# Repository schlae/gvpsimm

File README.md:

# GVP 64-pin SIMM modules

This repository contains reproduction SIMMs for GVP (Great Valley Products)
Amiga accelerator cards. Select a link below to pick a particular version.

[4MB version](4MB/README.md)

[16MB version](16MB/README.md)

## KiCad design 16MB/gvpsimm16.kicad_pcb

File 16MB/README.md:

# GVP-Compatible 64-Pin 16MB SIMM

*Warning: Beta Version! This has not been fabricated nor tested, build at your own risk*

This is a 16MB (4Mx32) SIMM design for certain GVP accelerator cards. It's
64-pin but follows the proprietary GVP pinout.

Since this is a beta version, fab files have not been generated. If you have
the expertise to get the files, load them in KiCad, and generate the fab
files, you're probably OK with doing some experimentation to get these working.

Board dimensions are 3.85 x 0.925 inches. It is a 4 layer board. When
ordering, **please specify a board thickness of 1.2mm!** This ensures that
it will fit in the SIMM slot. Again, to emphasize: most quick-turn board
services use 1.6mm thick boards by default which will not fit in a SIMM
slot. Be sure to select 1.2mm!

## DRAM Chips

KM44C4000AS-6, K4F1704110-FC60, HYB5116400BJ-60, or equivalent 60ns fast
page mode memory chips (16 megabit).

Be sure that the memory chip you select has a 12-bit row address and a 10-bit
column address -- sometimes known as "4K refresh" because a full refresh
must access all 4096 row addresses. It must also operate at 5V.

## Bypass Capacitors

Use eight 0603 capacitors with a value of at least 0.22uF. Ensure the voltage
rating is 10V or higher. Do not use 6.3V rated capacitors since they are too
close to the rail voltage of 5V.

## Assembly Notes

Since the chips are fairly close together, I recommend ordering the boards
with a solder stencil and using solder paste with a reflow process (or
hot plate) to solder the components.

## License

This project is licensed under the CERN Open Hardware License Version 2 - Permissive.

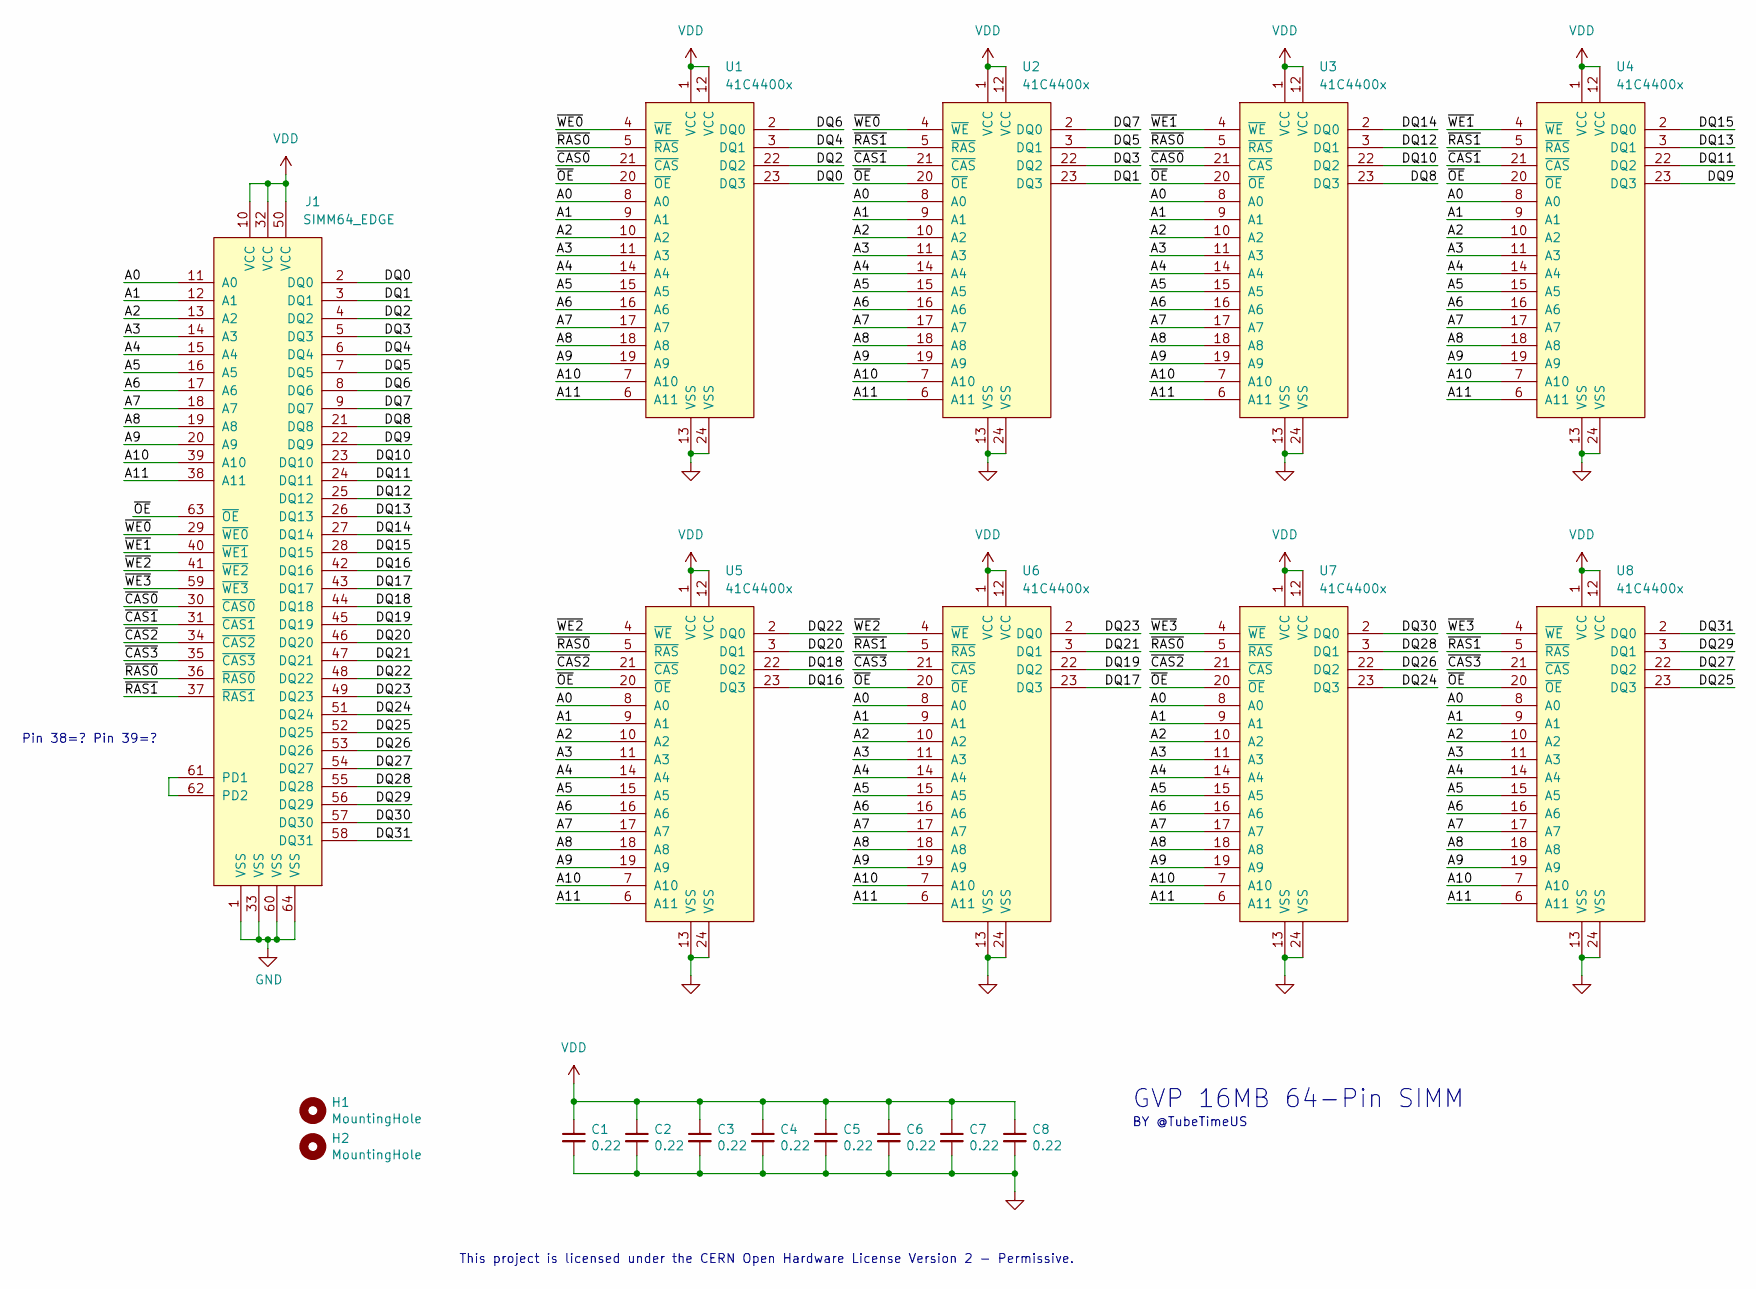
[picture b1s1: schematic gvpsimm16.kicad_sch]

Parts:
C1, C2, C3, C4, C5, C6, C7, C8: 0.22; CAPC1608X100
H1, H2: MountingHole; MH_125
J1: SIMM64_EDGE; EDGE_SIMM_64_127
U1, U2, U3, U4, U5, U6, U7, U8: 41C4400x; SOJ127P851X356-24

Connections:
/A0: J1.11 (A0), U1.8 (A0), U2.8 (A0), U3.8 (A0), U4.8 (A0), U5.8 (A0), U6.8 (A0), U7.8 (A0), U8.8 (A0)
/A1: J1.12 (A1), U1.9 (A1), U2.9 (A1), U3.9 (A1), U4.9 (A1), U5.9 (A1), U6.9 (A1), U7.9 (A1), U8.9 (A1)
/A2: J1.13 (A2), U1.10 (A2), U2.10 (A2), U3.10 (A2), U4.10 (A2), U5.10 (A2), U6.10 (A2), U7.10 (A2), U8.10 (A2)
/A3: J1.14 (A3), U1.11 (A3), U2.11 (A3), U3.11 (A3), U4.11 (A3), U5.11 (A3), U6.11 (A3), U7.11 (A3), U8.11 (A3)
/A4: J1.15 (A4), U1.14 (A4), U2.14 (A4), U3.14 (A4), U4.14 (A4), U5.14 (A4), U6.14 (A4), U7.14 (A4), U8.14 (A4)
/A5: J1.16 (A5), U1.15 (A5), U2.15 (A5), U3.15 (A5), U4.15 (A5), U5.15 (A5), U6.15 (A5), U7.15 (A5), U8.15 (A5)
/A6: J1.17 (A6), U1.16 (A6), U2.16 (A6), U3.16 (A6), U4.16 (A6), U5.16 (A6), U6.16 (A6), U7.16 (A6), U8.16 (A6)
/A7: J1.18 (A7), U1.17 (A7), U2.17 (A7), U3.17 (A7), U4.17 (A7), U5.17 (A7), U6.17 (A7), U7.17 (A7), U8.17 (A7)
/A8: J1.19 (A8), U1.18 (A8), U2.18 (A8), U3.18 (A8), U4.18 (A8), U5.18 (A8), U6.18 (A8), U7.18 (A8), U8.18 (A8)
/A9: J1.20 (A9), U1.19 (A9), U2.19 (A9), U3.19 (A9), U4.19 (A9), U5.19 (A9), U6.19 (A9), U7.19 (A9), U8.19 (A9)
/A10: J1.39 (A10), U1.7 (A10), U2.7 (A10), U3.7 (A10), U4.7 (A10), U5.7 (A10), U6.7 (A10), U7.7 (A10), U8.7 (A10)
/A11: J1.38 (A11), U1.6 (A11), U2.6 (A11), U3.6 (A11), U4.6 (A11), U5.6 (A11), U6.6 (A11), U7.6 (A11), U8.6 (A11)
/DQ0: J1.2 (DQ0), U1.23 (DQ3)
/DQ1: J1.3 (DQ1), U2.23 (DQ3)
/DQ2: J1.4 (DQ2), U1.22 (DQ2)
/DQ3: J1.5 (DQ3), U2.22 (DQ2)
/DQ4: J1.6 (DQ4), U1.3 (DQ1)
/DQ5: J1.7 (DQ5), U2.3 (DQ1)
/DQ6: J1.8 (DQ6), U1.2 (DQ0)
/DQ7: J1.9 (DQ7), U2.2 (DQ0)
/DQ8: J1.21 (DQ8), U3.23 (DQ3)
/DQ9: J1.22 (DQ9), U4.23 (DQ3)
/DQ10: J1.23 (DQ10), U3.22 (DQ2)
/DQ11: J1.24 (DQ11), U4.22 (DQ2)
/DQ12: J1.25 (DQ12), U3.3 (DQ1)
/DQ13: J1.26 (DQ13), U4.3 (DQ1)
/DQ14: J1.27 (DQ14), U3.2 (DQ0)
/DQ15: J1.28 (DQ15), U4.2 (DQ0)
/DQ16: J1.42 (DQ16), U5.23 (DQ3)
/DQ17: J1.43 (DQ17), U6.23 (DQ3)
/DQ18: J1.44 (DQ18), U5.22 (DQ2)
/DQ19: J1.45 (DQ19), U6.22 (DQ2)
/DQ20: J1.46 (DQ20), U5.3 (DQ1)
/DQ21: J1.47 (DQ21), U6.3 (DQ1)
/DQ22: J1.48 (DQ22), U5.2 (DQ0)
/DQ23: J1.49 (DQ23), U6.2 (DQ0)
/DQ24: J1.51 (DQ24), U7.23 (DQ3)
/DQ25: J1.52 (DQ25), U8.23 (DQ3)
/DQ26: J1.53 (DQ26), U7.22 (DQ2)
/DQ27: J1.54 (DQ27), U8.22 (DQ2)
/DQ28: J1.55 (DQ28), U7.3 (DQ1)
/DQ29: J1.56 (DQ29), U8.3 (DQ1)
/DQ30: J1.57 (DQ30), U7.2 (DQ0)
/DQ31: J1.58 (DQ31), U8.2 (DQ0)
/~CAS0: J1.30 (~CAS0), U1.21 (~CAS), U3.21 (~CAS)
/~CAS1: J1.31 (~CAS1), U2.21 (~CAS), U4.21 (~CAS)
/~CAS2: J1.34 (~CAS2), U5.21 (~CAS), U7.21 (~CAS)
/~CAS3: J1.35 (~CAS3), U6.21 (~CAS), U8.21 (~CAS)
/~OE: J1.63 (~OE), U1.20 (~OE), U2.20 (~OE), U3.20 (~OE), U4.20 (~OE), U5.20 (~OE), U6.20 (~OE), U7.20 (~OE), U8.20 (~OE)
/~RAS0: J1.36 (~RAS0), U1.5 (~RAS), U3.5 (~RAS), U5.5 (~RAS), U7.5 (~RAS)
/~RAS1: J1.37 (~RAS1), U2.5 (~RAS), U4.5 (~RAS), U6.5 (~RAS), U8.5 (~RAS)
/~WE0: J1.29 (~WE0), U1.4 (~WE), U2.4 (~WE)
/~WE1: J1.40 (~WE1), U3.4 (~WE), U4.4 (~WE)
/~WE2: J1.41 (~WE2), U5.4 (~WE), U6.4 (~WE)
/~WE3: J1.59 (~WE3), U7.4 (~WE), U8.4 (~WE)
GND: C1.2, C2.2, C3.2, C4.2, C5.2, C6.2, C7.2, C8.2, J1.1 (VSS), J1.33 (VSS), J1.60 (VSS), J1.64 (VSS), U1.13 (VSS), U1.24 (VSS), U2.13 (VSS), U2.24 (VSS), U3.13 (VSS), U3.24 (VSS), U4.13 (VSS), U4.24 (VSS), U5.13 (VSS), U5.24 (VSS), U6.13 (VSS), U6.24 (VSS), U7.13 (VSS), U7.24 (VSS), U8.13 (VSS), U8.24 (VSS)
unnamed: J1.61 (PD1), J1.62 (PD2)
VDD: C1.1, C2.1, C3.1, C4.1, C5.1, C6.1, C7.1, C8.1, J1.10 (VCC), J1.32 (VCC), J1.50 (VCC), U1.1 (VCC), U1.12 (VCC), U2.1 (VCC), U2.12 (VCC), U3.1 (VCC), U3.12 (VCC), U4.1 (VCC), U4.12 (VCC), U5.1 (VCC), U5.12 (VCC), U6.1 (VCC), U6.12 (VCC), U7.1 (VCC), U7.12 (VCC), U8.1 (VCC), U8.12 (VCC)

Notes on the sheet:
Pin 38=? Pin 39=?
BY @TubeTimeUS
This project is licensed under the CERN Open Hardware License Version 2 - Permissive.
GVP 16MB 64-Pin SIMM

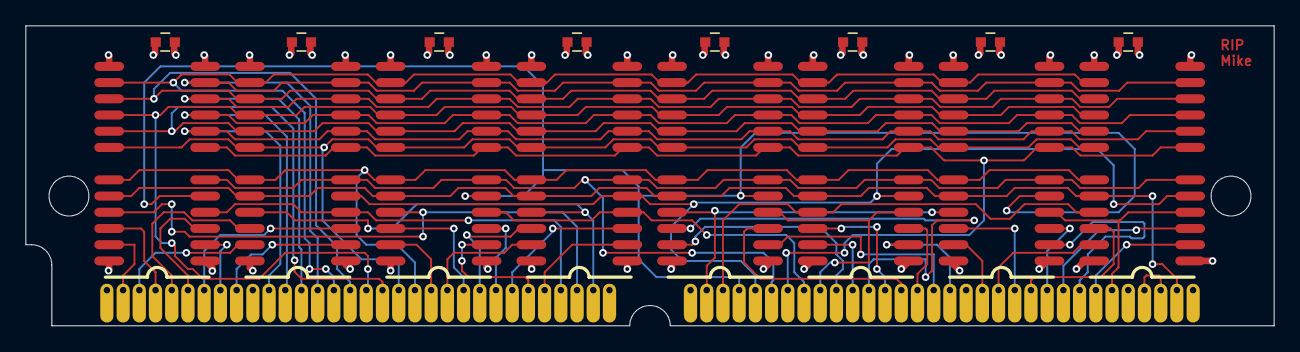
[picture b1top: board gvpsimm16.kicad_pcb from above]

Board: 4 copper layers, 97.8 x 23.5 mm, 19 parts (0 on the bottom side), 58 nets.

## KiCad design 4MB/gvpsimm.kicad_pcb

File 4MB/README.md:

# GVP-Compatible 64-Pin 4MB SIMM

GVP (Great Valley Products) made a number of Amiga accelerator cards back
in the 80s and 90s. Many of the accelerator cards accept 64-pin
memory modules; however they do not follow a standard pinout.

These GVP proprietary SIMMS are somewhat hard to find and expensive when
they do turn up. Others have reverse engineered the design, but these clones
use CAD tools that are not open source.

This design is based on a 4MB SIMM that came from my own GVP 68030
accelerator card. You can see my [epic build thread on Twitter](https://twitter.com/TubeTimeUS/status/1154195947125002240).

(The original SIMM is on the right, and on the left are my clones.)

Design files are here:

[Schematic](gvpsimm.pdf)

[Fab files](fab/gvpsimm_rev1.zip)

Board dimensions are 3.85 x 0.875 inches, and it is a 4 layer board. When
ordering the board, remember to specify a board thickness of 1.2mm. This
ensures it will fit in the SIMM slot.

## DRAM Chips

My original SIMM module uses the Hitachi HM514400CS-6 memory chips, which
are 1 Meg x 4 bit 60ns devices. Since there are eight memory chips, this
results in a memory array of 1 Meg x 32 bit, or 4 megabytes. I have built and
tested a large number of SIMMs with these chips and they all work fine.

There exist a number of memory chips which I have not tested (beware!) but are
likely compatible:
* Samsung KM44C1000DJ-6
* Mitsubishi M5M44400CJ-6
* NEC PD424400LA-60
* Toshiba TC514400ASJ-60
* TI TMS44400-60 DJ
* Micron MT4C4001JDJ-6

The list is from [this thread at Abime](http://eab.abime.net/showthread.php?t=86182).

## 1MB Variant

There exist 256K x 4 bit memories in the same package that are pin
compatible with the larger chip, and it can be installed instead,
yielding a 1MB SIMM. The difference is that pin 5 (A9 address line) is a
no-connect. I have not tested this configuration, but if you want to try it, I
found a couple of memory chips that might work.

* Samsung KM44C256DJ-6
* TI TMS44C256-60 DJ
* Mitsubishi M5M44256AJ-6

## Bypass Capacitors

Others have mistakenly assumed that the original GVP SIMM has no bypass
capacitors. This is not true--on detailed inspection I observed eight
ultra-low profile ceramic capacitors soldered directly underneath the
memory chips.

Ultra-low profile ceramic capacitors are hard to find now, and would
make assembly somewhat difficult. Instead of this I opted to use seven
standard 0603 ceramic capacitors placed in between the memory chips.
For best results, use 0.22uF or larger. Ensure the voltage rating is 10V
or higher, as 6.3V ceramics do not have sufficient derating for use at 5V.
Consider also that the capacitance of many ceramic capacitors decreases
significantly as the operating voltage nears the rated voltage, as much as
40%!

## Fabrication Notes

When you send the board out for fabrication, please specify a board
thickness of 1.2mm instead of the more common 1.6mm thickness. This
will ensure that the SIMM will fit correctly in the sockets.

Since the components are packed relatively close together, they can be
difficult to solder by hand. I recommend using a solder stencil and a
reflow process.

## License

This project is licensed under the CERN Open Hardware License Version 2 - Permissive.

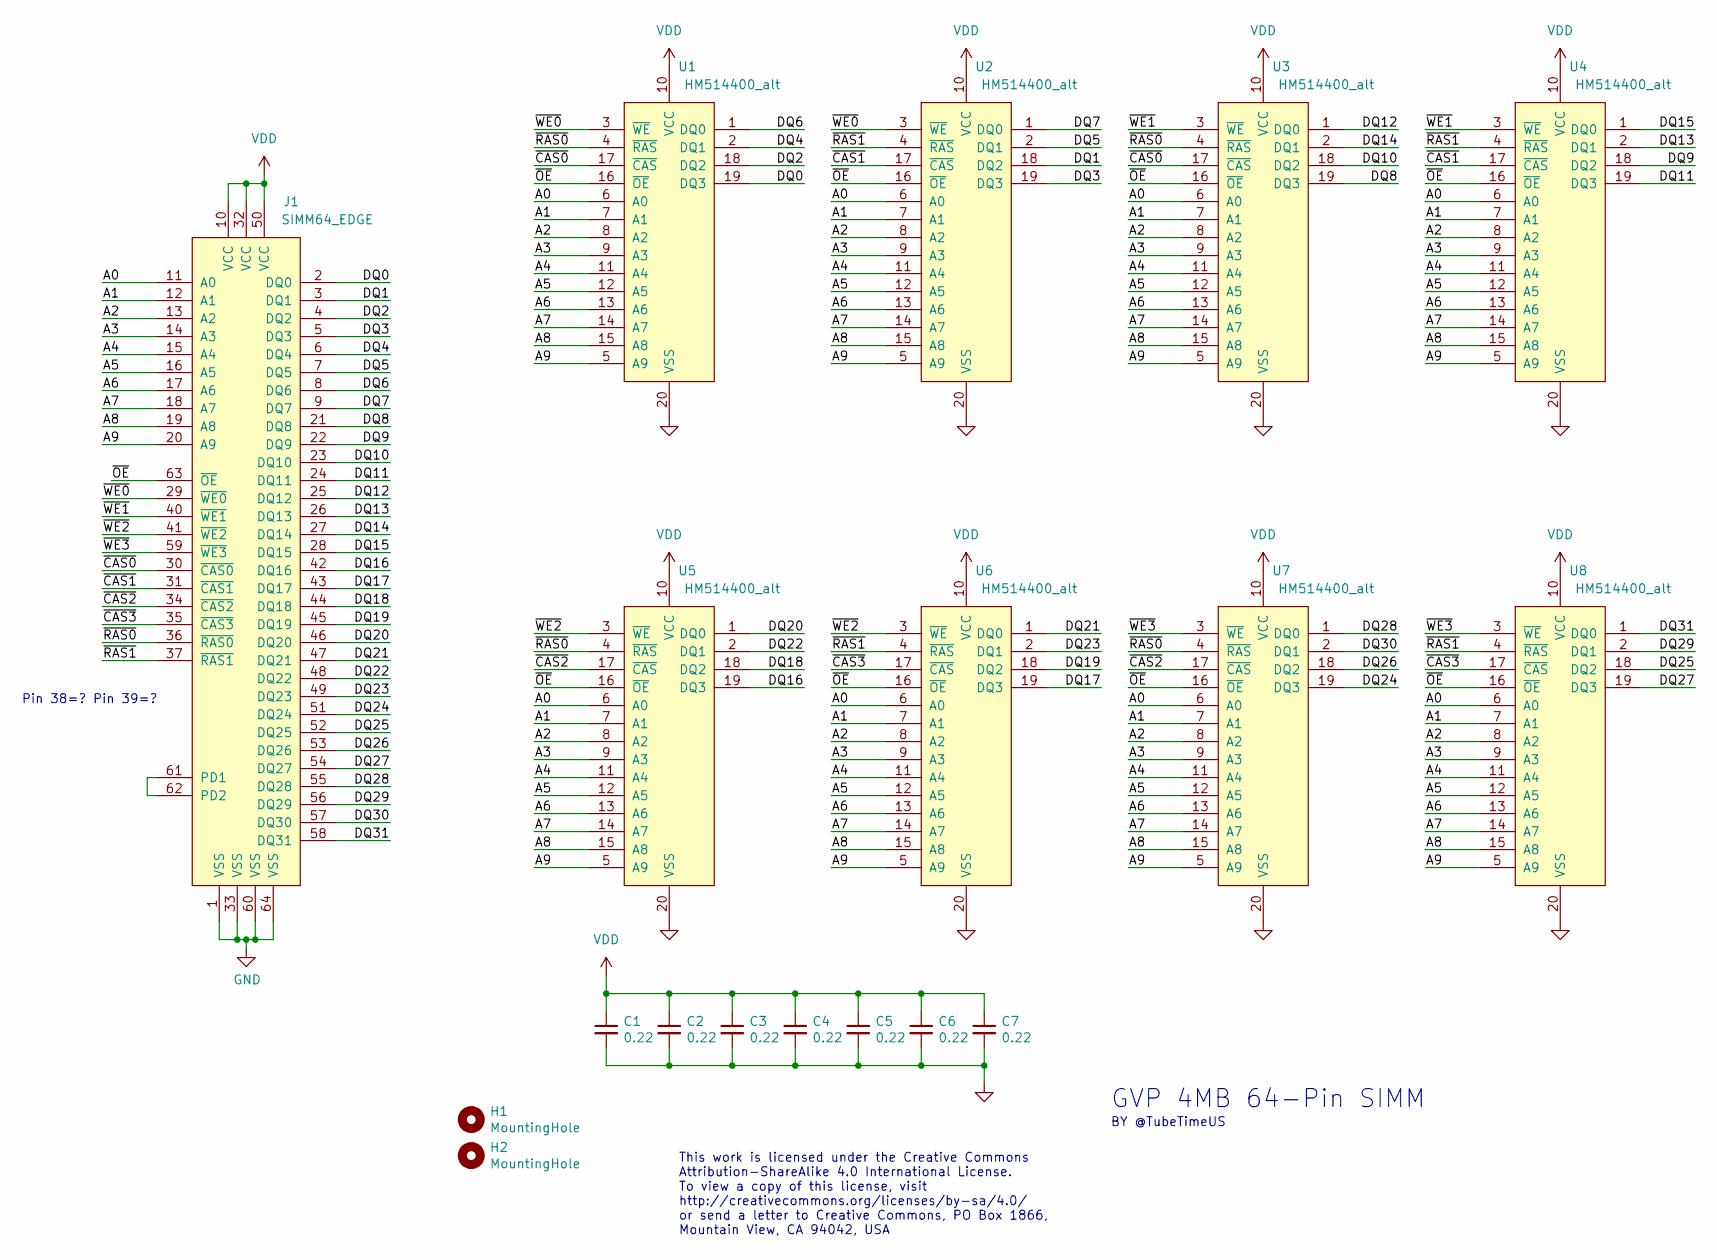
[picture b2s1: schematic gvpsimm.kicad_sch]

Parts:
C1, C2, C3, C4, C5, C6, C7: 0.22; CAPC1608X100
H1, H2: MountingHole; MH_125
J1: SIMM64_EDGE; EDGE_SIMM_64_127
U1, U2, U3, U4, U5, U6, U7, U8: HM514400_alt; SOJ127P851X356-20_alt; MPN HM514400CS-6 OR EQUIV

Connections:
/A0: J1.11 (A0), U1.6 (A0), U2.6 (A0), U3.6 (A0), U4.6 (A0), U5.6 (A0), U6.6 (A0), U7.6 (A0), U8.6 (A0)
/A1: J1.12 (A1), U1.7 (A1), U2.7 (A1), U3.7 (A1), U4.7 (A1), U5.7 (A1), U6.7 (A1), U7.7 (A1), U8.7 (A1)
/A2: J1.13 (A2), U1.8 (A2), U2.8 (A2), U3.8 (A2), U4.8 (A2), U5.8 (A2), U6.8 (A2), U7.8 (A2), U8.8 (A2)
/A3: J1.14 (A3), U1.9 (A3), U2.9 (A3), U3.9 (A3), U4.9 (A3), U5.9 (A3), U6.9 (A3), U7.9 (A3), U8.9 (A3)
/A4: J1.15 (A4), U1.11 (A4), U2.11 (A4), U3.11 (A4), U4.11 (A4), U5.11 (A4), U6.11 (A4), U7.11 (A4), U8.11 (A4)
/A5: J1.16 (A5), U1.12 (A5), U2.12 (A5), U3.12 (A5), U4.12 (A5), U5.12 (A5), U6.12 (A5), U7.12 (A5), U8.12 (A5)
/A6: J1.17 (A6), U1.13 (A6), U2.13 (A6), U3.13 (A6), U4.13 (A6), U5.13 (A6), U6.13 (A6), U7.13 (A6), U8.13 (A6)
/A7: J1.18 (A7), U1.14 (A7), U2.14 (A7), U3.14 (A7), U4.14 (A7), U5.14 (A7), U6.14 (A7), U7.14 (A7), U8.14 (A7)
/A8: J1.19 (A8), U1.15 (A8), U2.15 (A8), U3.15 (A8), U4.15 (A8), U5.15 (A8), U6.15 (A8), U7.15 (A8), U8.15 (A8)
/A9: J1.20 (A9), U1.5 (A9), U2.5 (A9), U3.5 (A9), U4.5 (A9), U5.5 (A9), U6.5 (A9), U7.5 (A9), U8.5 (A9)
/DQ0: J1.2 (DQ0), U1.19 (DQ3)
/DQ1: J1.3 (DQ1), U2.18 (DQ2)
/DQ2: J1.4 (DQ2), U1.18 (DQ2)
/DQ3: J1.5 (DQ3), U2.19 (DQ3)
/DQ4: J1.6 (DQ4), U1.2 (DQ1)
/DQ5: J1.7 (DQ5), U2.2 (DQ1)
/DQ6: J1.8 (DQ6), U1.1 (DQ0)
/DQ7: J1.9 (DQ7), U2.1 (DQ0)
/DQ8: J1.21 (DQ8), U3.19 (DQ3)
/DQ9: J1.22 (DQ9), U4.18 (DQ2)
/DQ10: J1.23 (DQ10), U3.18 (DQ2)
/DQ11: J1.24 (DQ11), U4.19 (DQ3)
/DQ12: J1.25 (DQ12), U3.1 (DQ0)
/DQ13: J1.26 (DQ13), U4.2 (DQ1)
/DQ14: J1.27 (DQ14), U3.2 (DQ1)
/DQ15: J1.28 (DQ15), U4.1 (DQ0)
/DQ16: J1.42 (DQ16), U5.19 (DQ3)
/DQ17: J1.43 (DQ17), U6.19 (DQ3)
/DQ18: J1.44 (DQ18), U5.18 (DQ2)
/DQ19: J1.45 (DQ19), U6.18 (DQ2)
/DQ20: J1.46 (DQ20), U5.1 (DQ0)
/DQ21: J1.47 (DQ21), U6.1 (DQ0)
/DQ22: J1.48 (DQ22), U5.2 (DQ1)
/DQ23: J1.49 (DQ23), U6.2 (DQ1)
/DQ24: J1.51 (DQ24), U7.19 (DQ3)
/DQ25: J1.52 (DQ25), U8.18 (DQ2)
/DQ26: J1.53 (DQ26), U7.18 (DQ2)
/DQ27: J1.54 (DQ27), U8.19 (DQ3)
/DQ28: J1.55 (DQ28), U7.1 (DQ0)
/DQ29: J1.56 (DQ29), U8.2 (DQ1)
/DQ30: J1.57 (DQ30), U7.2 (DQ1)
/DQ31: J1.58 (DQ31), U8.1 (DQ0)
/~CAS0: J1.30 (~CAS0), U1.17 (~CAS), U3.17 (~CAS)
/~CAS1: J1.31 (~CAS1), U2.17 (~CAS), U4.17 (~CAS)
/~CAS2: J1.34 (~CAS2), U5.17 (~CAS), U7.17 (~CAS)
/~CAS3: J1.35 (~CAS3), U6.17 (~CAS), U8.17 (~CAS)
/~OE: J1.63 (~OE), U1.16 (~OE), U2.16 (~OE), U3.16 (~OE), U4.16 (~OE), U5.16 (~OE), U6.16 (~OE), U7.16 (~OE), U8.16 (~OE)
/~RAS0: J1.36 (~RAS0), U1.4 (~RAS), U3.4 (~RAS), U5.4 (~RAS), U7.4 (~RAS)
/~RAS1: J1.37 (~RAS1), U2.4 (~RAS), U4.4 (~RAS), U6.4 (~RAS), U8.4 (~RAS)
/~WE0: J1.29 (~WE0), U1.3 (~WE), U2.3 (~WE)
/~WE1: J1.40 (~WE1), U3.3 (~WE), U4.3 (~WE)
/~WE2: J1.41 (~WE2), U5.3 (~WE), U6.3 (~WE)
/~WE3: J1.59 (~WE3), U7.3 (~WE), U8.3 (~WE)
GND: C1.2, C2.2, C3.2, C4.2, C5.2, C6.2, C7.2, J1.1 (VSS), J1.33 (VSS), J1.60 (VSS), J1.64 (VSS), U1.20 (VSS), U2.20 (VSS), U3.20 (VSS), U4.20 (VSS), U5.20 (VSS), U6.20 (VSS), U7.20 (VSS), U8.20 (VSS)
unnamed: J1.61 (PD1), J1.62 (PD2)
VDD: C1.1, C2.1, C3.1, C4.1, C5.1, C6.1, C7.1, J1.10 (VCC), J1.32 (VCC), J1.50 (VCC), U1.10 (VCC), U2.10 (VCC), U3.10 (VCC), U4.10 (VCC), U5.10 (VCC), U6.10 (VCC), U7.10 (VCC), U8.10 (VCC)

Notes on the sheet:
Pin 38=? Pin 39=?
BY @TubeTimeUS
This work is licensed under the Creative Commons Attribution-ShareAlike 4.0 International License. To view a copy of this license, visit http://creativecommons.org/licenses/by-sa/4.0/ or send a letter to Creative Commons, PO Box 1866, Mountain View, CA 94042, USA
GVP 4MB 64-Pin SIMM

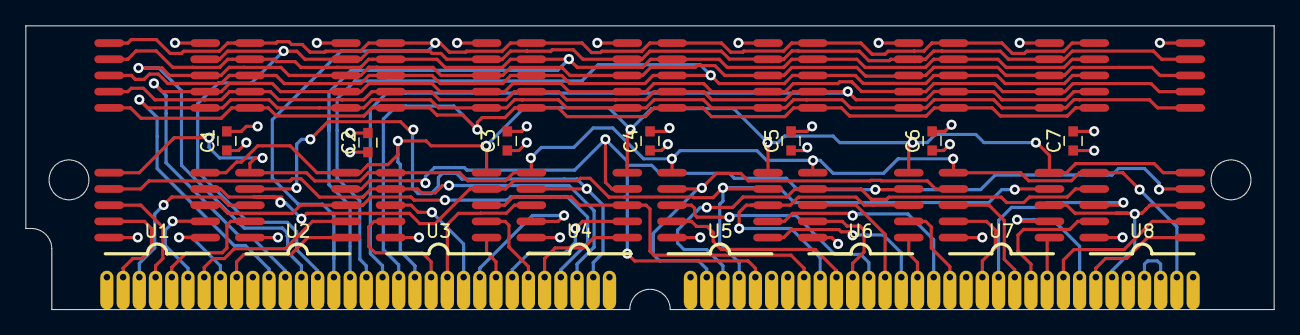
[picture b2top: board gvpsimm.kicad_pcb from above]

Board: 4 copper layers, 97.8 x 22.2 mm, 18 parts (0 on the bottom side), 56 nets.

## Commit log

2019-10-18 Empty commit.
2025-04-29 Update to KiCad 8
2025-04-29 Organize repository
2025-04-29 Modify license
2025-04-29 Added 16MB beta version
2025-04-29 Readme
2025-04-29 Update memory chip list

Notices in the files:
16MB/gvpsimm16.kicad_pcb:
© 2025 TUBETIMEUS
4MB/gvpsimm.kicad_pcb:
© 2019 TUBETIMEUS
